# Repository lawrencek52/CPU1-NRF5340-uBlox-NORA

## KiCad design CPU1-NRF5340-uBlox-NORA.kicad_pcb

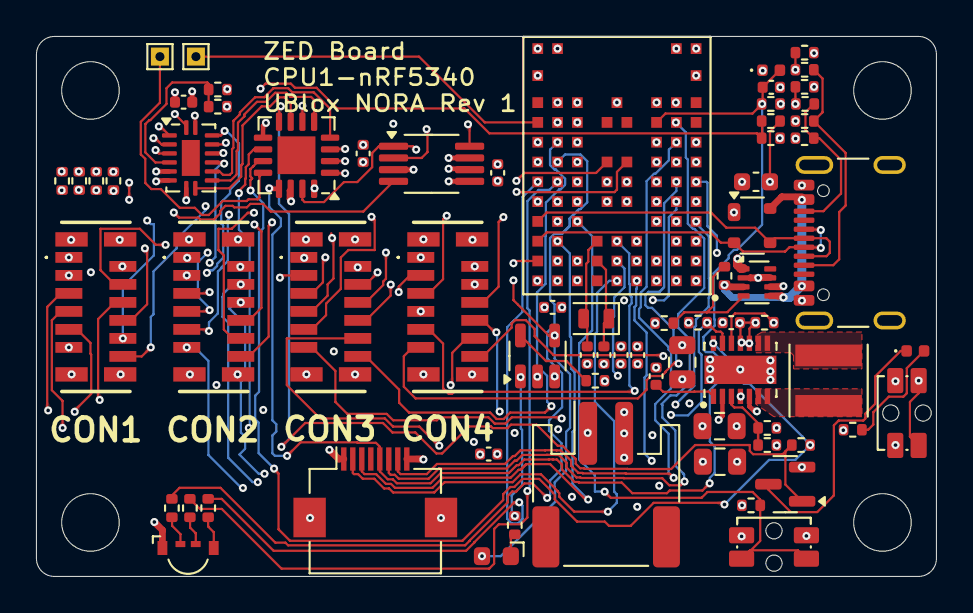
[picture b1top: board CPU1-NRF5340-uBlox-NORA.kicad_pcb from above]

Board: 6 copper layers, 50.0 x 30.0 mm, 75 parts (0 on the bottom side), 90 nets.

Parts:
C1, C11, C12: 0.1uF; C_0402_1005Metric
C2, C3, C4, C6, C9, C10, C15: 1uF; C_0402_1005Metric
C5: 4.7uF; C_0603_1608Metric
C7, C8: DNI; C_0402_1005Metric
C13, C14, C16: 47uF; C_0805_2012Metric
CON1, CON2, CON3, CON4: FH12-12S-0.5SVA_54_; FH1212S05SVA54
D1: SBR0240LPW-7B; D_0402_1005Metric
D2: PRTR5V0U2X; SOT-143
D3: A-SP136R6C-C01-3T RED; LED_0402_1005Metric
D4: EASV3015RGBA0; LED_RGB_Everlight_EASV3015RGBA0_Horizontal
D5: IN-S85CS5Y Yellow; LED_Kingbright_APA1606_1.6x0.6mm_Horizontal
H1, H2, H3, H4: MountingHole; MountingHole_3.2mm_M3_ISO14580
J1: GCT USB4105; USB_C_Receptacle_GCT_USB4105-xx-A_16P_TopMnt_Horizontal
J2: FH12-8S-0.5SH; Hirose_FH12-8S-0.5SH_1x08-1MP_P0.50mm_Horizontal
J3: S2B-PH-SM4-TB; JST_PH_S2B-PH-SM4-TB_1x02-1MP_P2.00mm_Horizontal
L1: 2.2uH 7.7A; IND_NRS4018T2R2MDGJ
Q1: BSS123; SOT-23
R1, R2, R3, R4, R5, R7, R8, R9, R16, R17, R18, R19, R21, R24: 100k; R_0402_1005Metric
R6, R29: 10k; R_0402_1005Metric
R10, R11: 5.1k; R_0402_1005Metric
R12, R13, R14, R15: 280k; R_0402_1005Metric
R20: 2.0k; R_0402_1005Metric
R22: 560k; R_0402_1005Metric
R23: 294; R_0402_1005Metric
R25: 39; R_0402_1005Metric
R26: 130; R_0402_1005Metric
R27: 30; R_0402_1005Metric
R28: 150; R_0402_1005Metric
SW1, SW2: SW_SPST_ALPS_SKSCLDE010
TP1, TP2: TestPoint; TestPoint_THTPad_1.0x1.0mm_Drill0.5mm
U1: 74HC4051BQ; DHVQFN-16-1EP_2.5x3.5mm_P0.5mm_EP1x2mm
U2: PCA9557BS; Texas_RGV0016A_VQFN-16-1EP_4x4mm_P0.65mm_EP2.1x2.1mm
U3: ADC081C021CIMM; MSOP-8_3x3mm_P0.65mm
U4: NORA-B106-00B; XCVR_NORA-B106-00B
U5: MCP73831T-2DCI/OT; SOT-23-5
U6: TPS2116DRL; SOT-583-8
U7: RT6154AGQW; VREG_RT6154AGQW
Y1: Crystal; Crystal_SMD_2012-2Pin_2.0x1.2mm

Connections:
+3.3V: C2.1, C3.1, C4.1, C6.1, C14.1, C15.1, C16.1, CON1.2, CON2.2, CON3.2, CON4.2, D1.1 (K), D4.1 (A), J2.1, R6.1, R22.1, R23.2, R29.1, U1.16 (VDD), U2.14 (VDD), U3.5 (VA), U4.A7 (VDD), U4.A8 (VDDH), U4.B7 (VDD), U7.4 (VOUT), U7.5 (VOUT__1)
/AIN0: CON1.4, U4.D8 (P0.04/AIN0)
/AIN1: CON1.5, U4.E8 (P0.05/AIN1)
/AIN2: CON1.6, U4.E7 (P0.06/AIN2)
/AIN3: CON1.7, U4.D3 (P0.07/AIN3)
/AIN4: CON1.8, U4.G3 (P0.25/AIN4)
/AIN5: CON1.9, U4.G2 (P0.26/AIN5)
/AIN6: CON1.10, U4.H3 (P0.27/AIN6)
/AIN7: CON1.11, U4.J8 (P0.28/AIN7)
/CC1: R3.2, R4.1, U1.2 (X6)
/CC2: R2.1, R9.2, U1.4 (X7)
/DISPON: Q1.1 (G), R24.1, U2.8 (IO3)
/DM: D2.3 (I/O2), J1.A7 (D-), J1.B7 (D-), U4.D9 (USB_DM)
/DP: D2.2 (I/O1), J1.A6 (D+), J1.B6 (D+), U4.C9 (USB_DP)
/FB: R21.1, R22.2, U7.3 (FB)
/HK-A0: U1.11 (A), U2.4 (IO0)
/HK-A1: U1.10 (B), U2.5 (IO1)
/HK-A2: U1.9 (C), U2.7 (IO2)
/HK-ADC0: CON1.3, R12.1, U1.13 (X0)
/HK-ADC1: CON2.3, R13.1, U1.14 (X1)
/HK-ADC2: CON3.3, R15.1, U1.15 (X2)
/HK-ADC3: CON4.3, R14.1, U1.12 (X3)
/LX1: L1.1, U7.8 (LX1), U7.9 (LX1__1)
/LX2: L1.2, U7.6 (LX2), U7.7 (LX2__1)
/P0.02-NFC1: CON4.9, U4.C5 (P0.02/NFC1)
/P0.03-NFC2: CON4.10, U4.B5 (P0.03/NFC2)
/P0.19: CON4.12, U4.F3 (P0.19)
/P0.21: CON3.9, U4.E3 (P0.21)
/P0.24: CON3.10, U4.H1 (P0.24)
/P0.29: CON3.11, U4.H7 (P0.29)
/P0.30: CON3.12, U4.H8 (P0.30)
/P0.31: TP2.1, U4.J9 (P0.31)
/P1.00: CON2.6, U4.A4 (P1.00)
/P1.01: CON2.7, U4.C4 (P1.01)
/P1.04: CON2.8, U4.G4 (P1.04)
/P1.05: CON2.9, U4.E9 (P1.05)
/P1.06: CON2.10, U4.G1 (P1.06)
/P1.07: CON2.11, U4.F7 (P1.07)
/P1.08: CON2.12, U4.G5 (P1.08)
/P1.09: U2.15 (SCL), U3.1 (SCL), U4.G7 (P1.09)
/P1.10: U2.16 (SDA), U3.8 (SDA), U4.J7 (P1.10)
/P1.11: U3.2 (ALERT), U4.H9 (P1.11)
/P1.12: R25.2, U4.G8 (P1.12)
/P1.13: CON1.12, U4.G9 (P1.13)
/P1.14: R27.2, U4.F8 (P1.14)
/P1.15: R26.2, U4.F9 (P1.15)
/PGOOD: R24.2, U2.11 (IO6), U7.14 (PGOOD)
/PSEN: R18.1, U2.10 (IO5), U7.12 (EN)
/PSMODE: R17.1, U2.9 (IO4), U7.13 (PS/SYNC)
/QSPI-CSN: CON4.5, U4.E1 (P0.18/CSN)
/QSPI-IO0: CON4.6, U4.D2 (P0.13/IO0)
/QSPI-IO1: CON4.7, U4.E2 (P0.14/IO1)
/QSPI-IO2: CON4.8, U4.D1 (P0.15/IO2)
/QSPI-IO3: CON4.11, U4.F2 (P0.16/IO3)
/QSPI-SCK: CON4.4, U4.F1 (P0.17/SCK)
/RESET: C1.1, D1.2 (A), J2.5, R6.2, SW1.1 (A), SW1.2 (B), U2.13 (~RESET), U4.J3 (~RESET)
/RxD: J2.3, U4.C8 (P0.22)
/SCL: CON2.4, U4.A3 (P1.03/TWI)
/SDA: CON2.5, U4.B4 (P1.02/TWI)
/SPI-CS: CON3.5, U4.B3 (P0.11/TRACEDATA0/CSN)
/SPI-DCX: CON3.8, U4.A2 (P0.12/TRACECLK/DCX)
/SPI-MISO: CON3.6, U4.C1 (P0.10/TRACEDATA1/MISO)
/SPI-MOSI: CON3.7, U4.C2 (P0.09/TRACEDATA2/MOSI)
/SPI-SCK: CON3.4, U4.B1 (P0.08/TRACEDATA3/SCK)
/SWDCLK: J2.6, U4.J2 (SWDCLK)
/SWDIO: J2.7, U4.H2 (SWDIO)
/SYS: C11.1, C13.1, R18.2, U6.2 (VOUT), U6.7 (VOUT), U7.10 (VIN), U7.11 (VIN__1)
/TxD: J2.2, U4.A5 (P0.20)
/USER: R29.2, SW2.1 (A), SW2.2 (B), U4.D7 (P0.23)
/VBAT: C10.1, J3.1, R5.1, U5.3 (V_{BAT}), U6.6 (VIN2)
/VBATMON: R1.1, R5.2, U1.5 (X5)
/VBUS: C5.1, C9.1, D2.4 (VCC), D5.2 (A), J1.A4 (VBUS), J1.A9 (VBUS), J1.B4 (VBUS), J1.B9 (VBUS), R7.1, R19.1, U5.4 (V_{DD}), U6.3 (VIN1), U6.5 (MODE)
/VBUSMON: R7.2, R8.1, U1.1 (X4)
/VINA: C12.1, U7.1 (VINA)
/XL1: C8.1, U4.C6 (P0.00/XL1), Y1.2
/XL2: C7.1, U4.B6 (P0.01/XL2), Y1.1
GND: C1.2, C2.2, C3.2, C4.2, C5.2, C6.2, C7.2, C8.2, C9.2, C10.2, C11.2, C12.2, C13.2, C14.2, C15.2, C16.2, CON1.1, CON1.MP1, CON1.MP2, CON1.MP3, CON1.MP4, CON2.1, CON2.MP1, CON2.MP2, CON2.MP3, CON2.MP4, CON3.1, CON3.MP1, CON3.MP2, CON3.MP3, CON3.MP4, CON4.1, CON4.MP1, CON4.MP2, CON4.MP3, CON4.MP4, D2.1 (GND), J1.A1 (GND), J1.A12 (GND), J1.B1 (GND), J1.B12 (GND), J1.S1 (SHIELD), J2.8, J2.MP (MountPin), J3.2, Q1.2 (S), R1.2, R2.2, R4.2, R8.2, R10.1, R11.1, R12.2, R13.2, R14.2, R15.2, R16.2, R17.2, R20.2, R21.2, SW1.3 (A), SW1.4 (B), SW2.3 (A), SW2.4 (B), U1.6 (Inh), U1.7 (VEE), U1.8 (VSS), U2.1 (A0), U2.2 (A1), U2.3 (A2), U2.6 (VSS), U3.3 (ADR0), U3.6 (ADR1), U3.7 (GND), U4.A1 (VSS), U4.A9 (VSS), U4.B2 (VSS), U4.B8 (VSS), U4.E4 (VSS), U4.E5 (VSS), U4.F4 (VSS), U4.F5 (VSS), U4.K2 (VSS), U4.K3 (VSS), U4.K5 (VSS), U4.K7 (VSS), U4.K8 (VSS), U4.L1 (VSS), U4.L9 (VSS), U4.M1 (VSS), U4.M2 (VSS), U4.M8 (VSS), U4.M9 (VSS), U5.2 (V_{SS}), U6.1 (GND), U7.2 (GND), U7.15 (PGND)
unnamed: D3.2 (A), R23.1
unnamed: D3.1 (K), Q1.3 (D)
unnamed: D4.2 (BK), R25.1
unnamed: D4.3 (GK), R27.1
unnamed: D4.4 (RK), R26.1
unnamed: D5.1 (K), R28.2
unnamed: J1.A5 (CC1), R3.1, R10.2
unnamed: J1.B5 (CC2), R9.1, R11.2
unnamed: U1.3 (X), U3.4 (VIN)
unnamed: TP1.1, U2.12 (IO7)
unnamed: R20.1, U5.5 (PROG)
unnamed: R28.1, U5.1 (STAT)
unnamed: R16.1, R19.2, U6.4 (PR1)

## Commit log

2025-08-28 first save of project
2025-09-19 files after sent to Bittele, with corrections for Bittele
